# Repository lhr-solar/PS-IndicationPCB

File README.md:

# PS-IndicationPCB
Addressable LEDs for battery &amp; dashboard indication

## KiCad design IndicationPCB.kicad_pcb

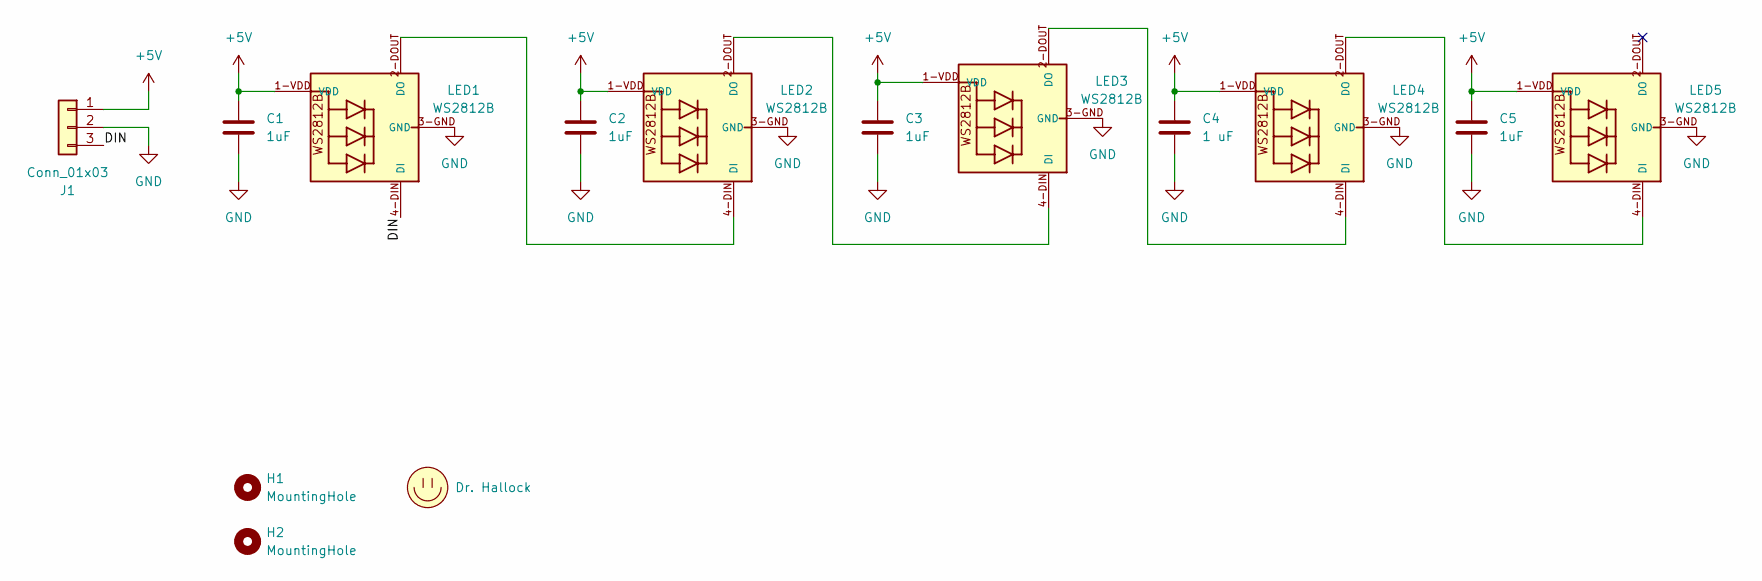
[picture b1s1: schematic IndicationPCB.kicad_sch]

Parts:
C1, C2, C3, C5: 1uF; C_0603_1608Metric_Pad1.08x0.95mm_HandSolder
C4: 1 uF; C_0603_1608Metric_Pad1.08x0.95mm_HandSolder
H1, H2: MountingHole; MountingHole_3.2mm_M3
J1: Conn_01x03; Molex_Nano-Fit_105309-xx03_1x03_P2.50mm_Vertical
LED1, LED2, LED3, LED4, LED5: WS2812B
LOGO1: Dr. Hallock; LHRs_LOGO

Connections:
+5V: C1.1, C2.1, C3.1, C4.1, C5.1, J1.1, LED1.1-VDD (VDD), LED2.1-VDD (VDD), LED3.1-VDD (VDD), LED4.1-VDD (VDD), LED5.1-VDD (VDD)
/DIN: J1.3, LED1.4-DIN (DI)
GND: C1.2, C2.2, C3.2, C4.2, C5.2, J1.2, LED1.3-GND (GND), LED2.3-GND (GND), LED3.3-GND (GND), LED4.3-GND (GND), LED5.3-GND (GND)
unnamed: LED1.2-DOUT (DO), LED2.4-DIN (DI)
unnamed: LED2.2-DOUT (DO), LED3.4-DIN (DI)
unnamed: LED3.2-DOUT (DO), LED4.4-DIN (DI)
unnamed: LED4.2-DOUT (DO), LED5.4-DIN (DI)

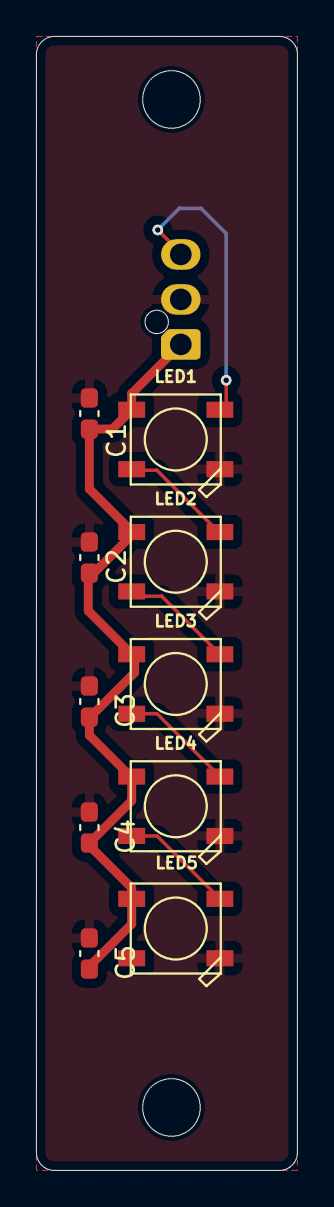
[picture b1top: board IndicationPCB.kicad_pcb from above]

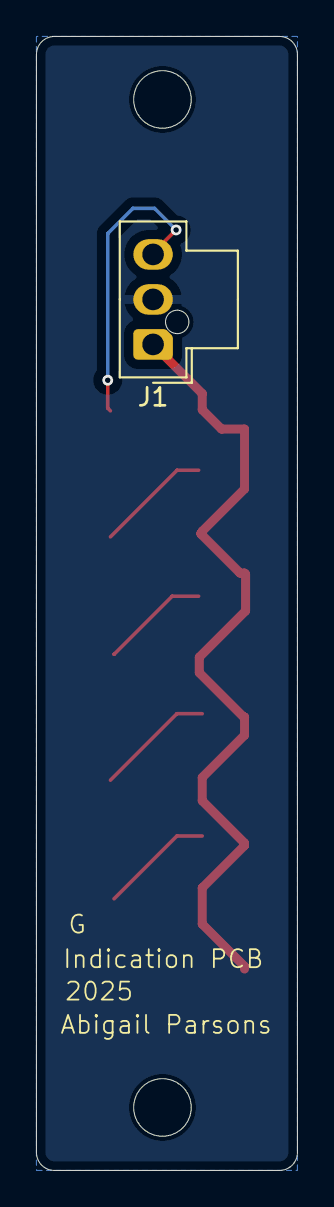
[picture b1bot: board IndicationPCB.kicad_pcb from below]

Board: 2 copper layers, 14.5 x 63.0 mm, 14 parts (2 on the bottom side), 7 nets.

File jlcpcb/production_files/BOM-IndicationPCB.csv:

<<<<<<< HEAD
Description (Customer #),Quantity,P/N,,,,,,,,,
WS2812B  Adressable LEDs ,5,WS2812B,,,,,,,,,
Capacitor 1uF 0603,5,MLASU168SB5105KTNA01,,,,,,,,,
Molex Nanofit 1x3 Horizontal,1,105313-1103,,,,,,,,,
,,,,,,,,,,,
,,,,,,,,,,,
,,,,,,,,,,,
,,,,,,,,,,,
,,,,,,,,,,,
,,,,,,,,,,,
,,,,,,,,,,,
,,,,,,,,,,,
,,,,,,,,,,,
,,,,,,,,,,,
,,,,,,,,,,,
,,,,,,,,,,,
,,,,,,,,,,,
,,,,,,,,,,,
,,,,,,,,,,,
,,,,,,,,,,,
,,,,,,,,,,,
,,,,,,,,,,,
,,,,,,,,,,,
,,,,,,,,,,,
=======
Comment,Designator,Footprint,LCSC,Quantity
WS2812B,LED2,WS2812B,,1
WS2812B,LED1,WS2812B,,1
1uF,C2,C_0603_1608Metric_Pad1.08x0.95mm_HandSolder,,1
WS2812B,LED3,WS2812B,,1
1uF,C3,C_0603_1608Metric_Pad1.08x0.95mm_HandSolder,,1
WS2812B,LED4,WS2812B,,1
1 uF,C4,C_0603_1608Metric_Pad1.08x0.95mm_HandSolder,,1
Conn_01x03,J1,Molex_Nano-Fit_105309-xx03_1x03_P2.50mm_Vertical,,1
1uF,C1,C_0603_1608Metric_Pad1.08x0.95mm_HandSolder,,1
1uF,C5,C_0603_1608Metric_Pad1.08x0.95mm_HandSolder,,1
WS2812B,LED5,WS2812B,,1
Dr. Hallock,LOGO1,LHRs_LOGO,,1
>>>>>>> 91abbcbd193afbd1e28e1f3d279eb04204023598

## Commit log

2025-08-30 Initial
2025-09-06 Finished Draft??
2025-09-13 Draft
2025-09-13 curved the edges :D
2025-09-13 correct LEDS
2025-09-13 add submodule
2025-09-15 KiCAD-Sharepoint
2025-09-15 Added Models
2025-09-15 add Models
2025-09-16 fixed
2025-09-16 submodule
2025-09-16 logo!
2025-09-16 gerber
2025-10-06 Rev a (#1)
    * Initial
    * Finished Draft??
    * Draft
    * curved the edges :D
    * correct LEDS
    * KiCAD-Sharepoint
2025-10-13 removed folder inside folder
2025-10-13 readd kicad sharepoint
2025-10-13 new connector
2025-10-14 fix connector model
2025-10-14 new gerbs
2025-10-25 bom and gerber
